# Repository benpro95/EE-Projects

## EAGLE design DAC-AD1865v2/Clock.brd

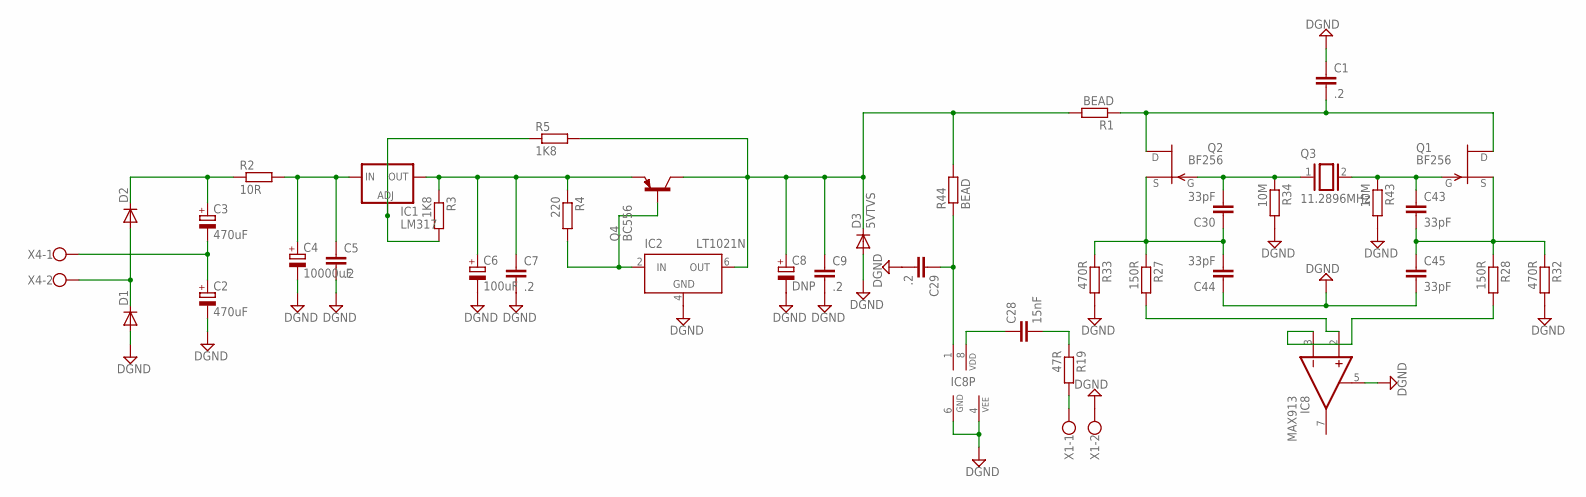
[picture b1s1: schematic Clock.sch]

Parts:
C1, C5, C7, C9, C29: .2; C1210K
C2, C3: 470uF; E5-10,5
C4: 10000uF; E7,5-16
C6: 100uF; E3,5-8
C8: DNP; E3,5-8
C28: 15nF; C050-055X075
C30, C43, C44, C45: 33pF; C050-030X075
D1, D2: 1N4148DO35-7; DO35-7
D3: 5VTVS; DO204-10
IC1: LM317; 317TS
IC2: LT1021N; DIL08
IC8: MAX913; DIL08
Q1, Q2: BF256; TO92-
Q3: 11.2896MHz; QS
Q4: BC556; TO92-EBC
R1, R44: BEAD; R1210
R2: 10R; 0207/10
R3, R5: 1K8; 0204/7
R4: 220; 0204/7
R19: 47R; R1210
R27, R28: 150R; 0204/7
R32, R33: 470R; 0204/7
R34, R43: 10M; 0204/7
X1, X4: W237-02P; W237-132

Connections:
DGND: C1.1, C2.-, C4.-, C5.2, C6.-, C7.2, C8.-, C9.2, C29.2, C44.1, C45.2, D1.A, D3.A, IC2.4 (GND), IC8.4 (VEE), IC8.5 (LATCH), IC8.6 (GND), R32.2, R33.2, R34.2, R43.2, X1.2
unnamed: C29.1, IC8.1 (VCC), R44.1
unnamed: C2.+, C3.-, X4.1
unnamed: C4.+, C5.1, IC1.3 (IN), R2.2
unnamed: C3.+, D2.C, R2.1
unnamed: D1.C, D2.A, X4.2
unnamed: C6.+, C7.1, IC1.2 (OUT), Q4.E, R3.1, R4.1
unnamed: IC1.1 (ADJ), R3.2, R5.1
unnamed: IC2.2 (IN), Q4.B, R4.2
unnamed: C8.+, C9.1, D3.C, IC2.6 (OUT), Q4.C, R1.2, R5.2, R44.2
unnamed: R19.2, X1.1
unnamed: C28.1, IC8.8 (VDD)
unnamed: C28.2, R19.1
unnamed: C30.1, C44.2, Q2.2 (S), R27.1, R33.1
unnamed: IC8.2 (+IN), R27.2
unnamed: IC8.3 (-IN), R28.2
unnamed: C1.2, Q1.3 (D), Q2.3 (D), R1.1
unnamed: C43.2, C45.1, Q1.2 (S), R28.1, R32.1
unnamed: C30.2, Q2.1 (G), Q3.1, R34.1
unnamed: C43.1, Q1.1 (G), Q3.2, R43.1

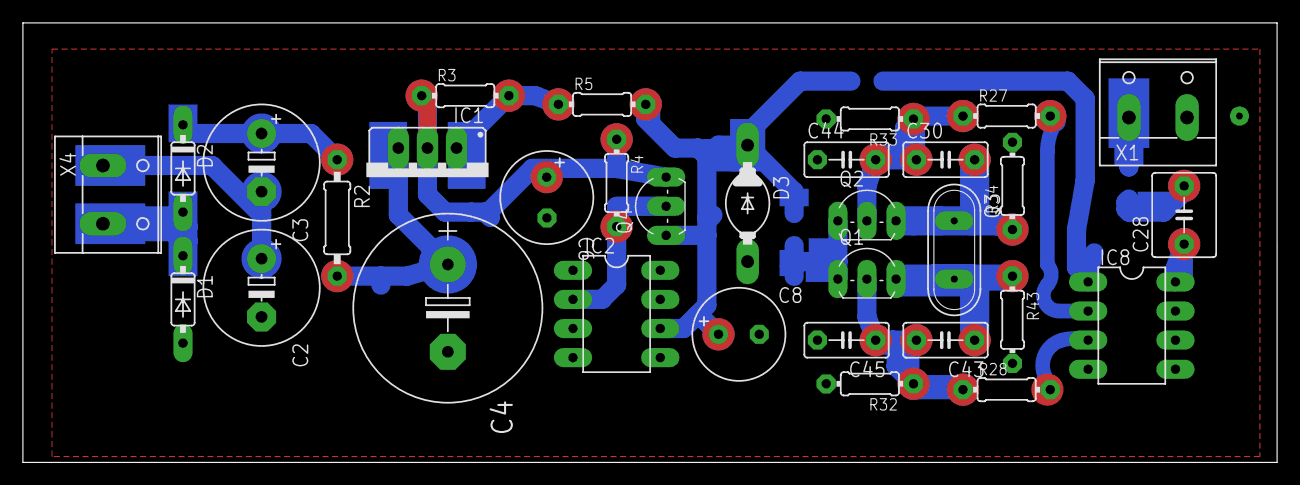
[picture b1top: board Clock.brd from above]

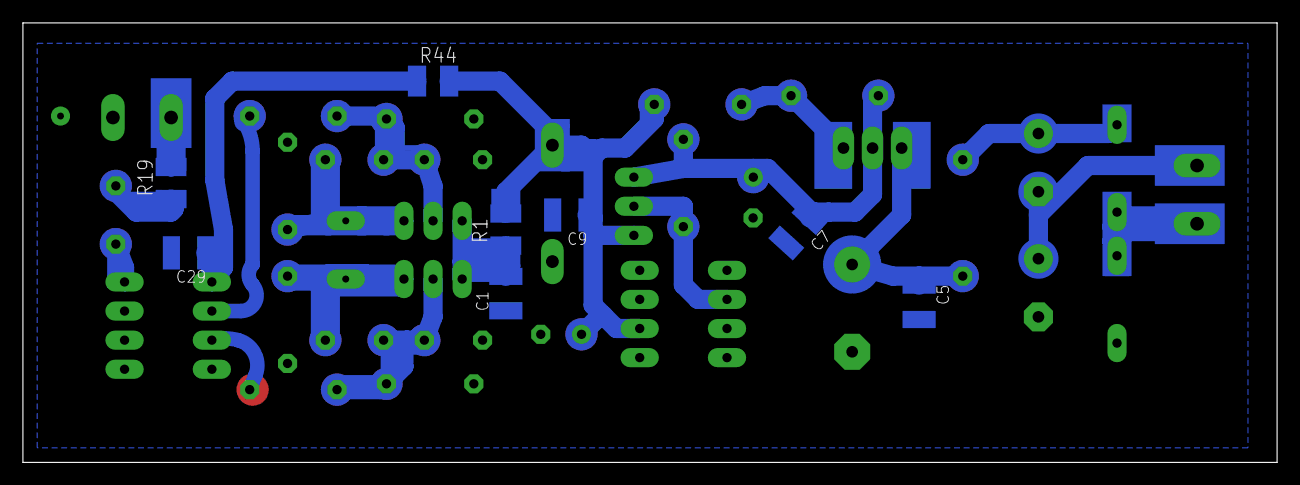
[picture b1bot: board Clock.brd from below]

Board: 2 copper layers, 109.5 x 38.4 mm, 40 parts (8 on the bottom side), 20 nets.
